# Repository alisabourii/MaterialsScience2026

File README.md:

# MaterialsScience2026

###Tinkercad Protetip

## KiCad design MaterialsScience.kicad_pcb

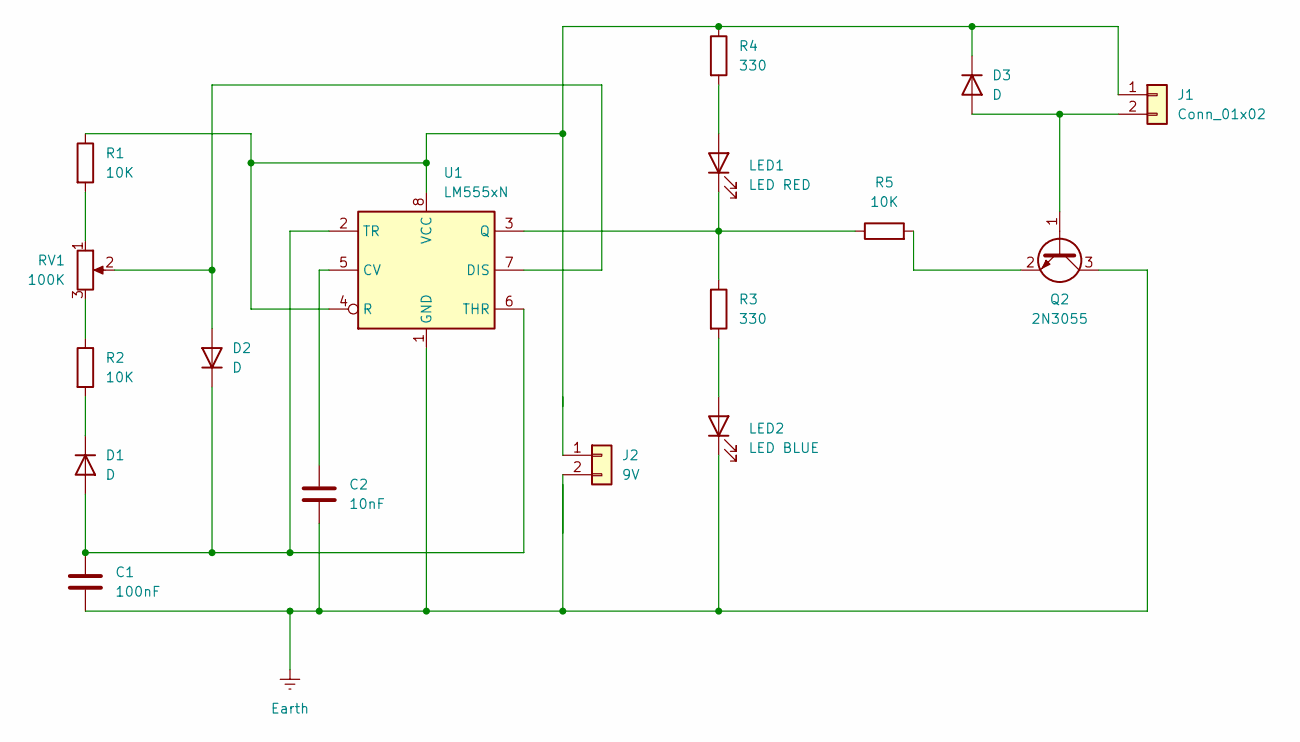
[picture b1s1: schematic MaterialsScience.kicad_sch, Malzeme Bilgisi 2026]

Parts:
C1: 100nF; C_Disc_D5.0mm_W2.5mm_P2.50mm
C2: 10nF; C_Disc_D5.0mm_W2.5mm_P2.50mm
D1, D2, D3: D; D_DO-41_SOD81_P10.16mm_Horizontal
J1: Conn_01x02; PinHeader_1x02_P2.54mm_Vertical
J2: 9V; PinHeader_1x02_P2.54mm_Vertical
LED1: LED RED; LED_D5.0mm
LED2: LED BLUE; LED_D5.0mm
Q2: 2N3055; TO-3
R1, R2, R5: 10K; R_Axial_DIN0207_L6.3mm_D2.5mm_P7.62mm_Horizontal
R3, R4: 330; R_Axial_DIN0207_L6.3mm_D2.5mm_P7.62mm_Horizontal
RV1: 100K; Potentiometer_Bourns_3296W_Vertical
U1: LM555xN; DIP-8_W7.62mm

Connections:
Earth: C1.2, C2.2, LED2.1 (K), Q2.3 (C), U1.1 (GND)
unnamed: C1.1, D1.2 (A), D2.1 (K), U1.2 (TR), U1.6 (THR)
unnamed: D1.1 (K), R2.2
unnamed: D2.2 (A), RV1.2, U1.7 (DIS)
unnamed: D3.2 (A), J1.2, Q2.1 (B)
unnamed: D3.1 (K), J1.1, R1.1, R4.1, U1.4 (R), U1.8 (VCC)
unnamed: LED1.2 (A), R4.2
unnamed: LED1.1 (K), R3.1, R5.1, U1.3 (Q)
unnamed: LED2.2 (A), R3.2
unnamed: Q2.2 (E), R5.2
unnamed: R1.2, RV1.1
unnamed: R2.1, RV1.3
unnamed: C2.1, U1.5 (CV)

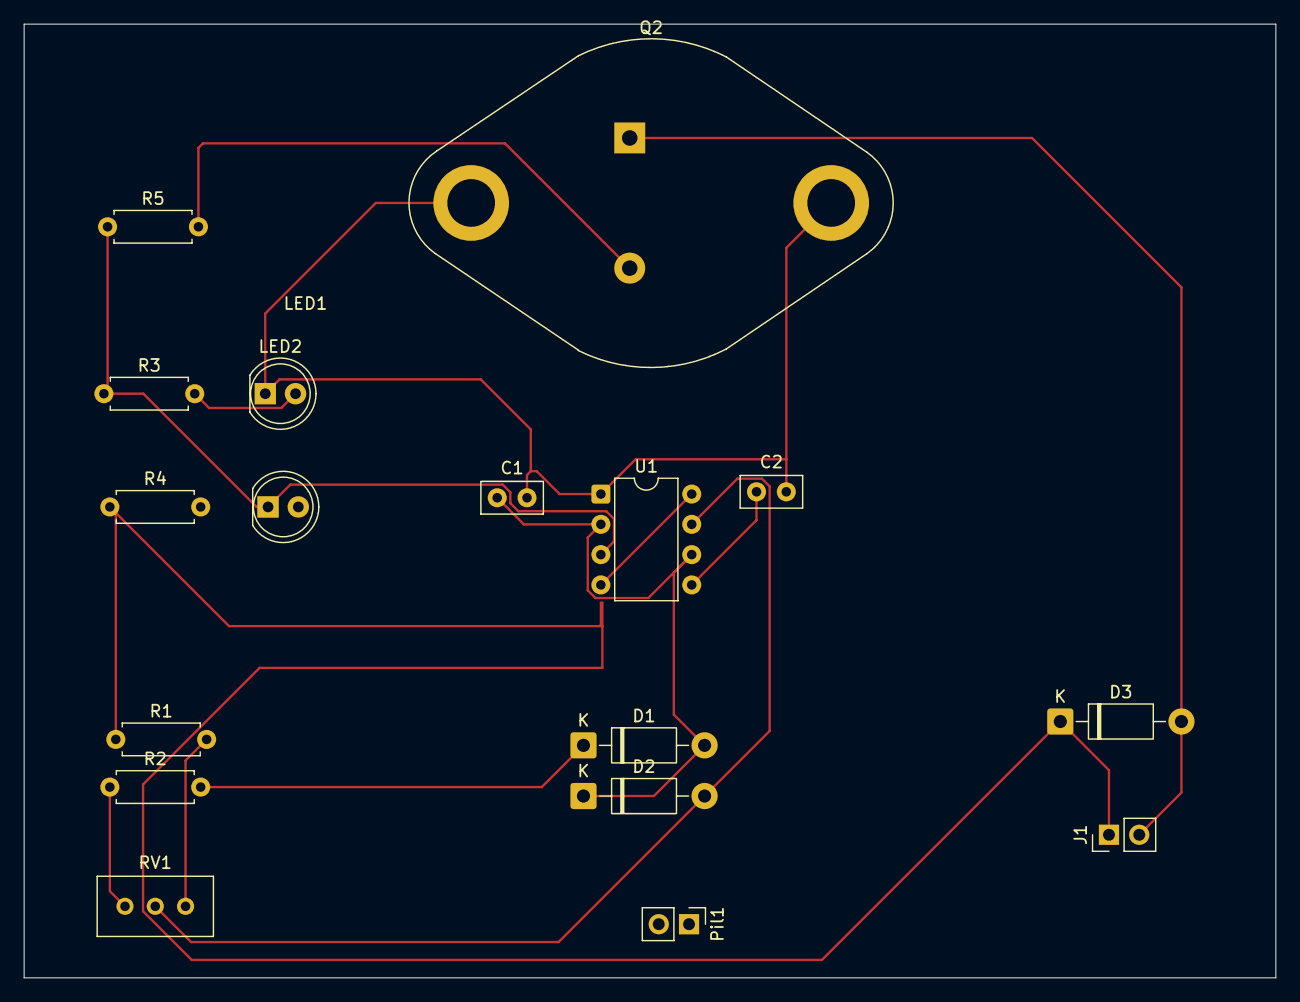
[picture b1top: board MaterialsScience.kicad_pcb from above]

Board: 2 copper layers, 105.0 x 80.0 mm, 17 parts (0 on the bottom side), 13 nets.

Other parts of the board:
Pil1: 9V; PinHeader_1x02_P2.54mm_Vertical

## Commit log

2026-05-01 PCB Shematich
2026-05-02 desin PCB
2026-05-02 Add new image to README
    Added an additional image to the README.
